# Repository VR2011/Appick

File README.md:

Appick is a 4-key macropad that allows you to launch an app from a click of a button! It's loaded to launch Brave, Spotify, Steam, and Discord. It also features an OLED display that displays what app is being launched!

**You'll need to install AutoHotkey for this to work as intended. Install it [here](https://www.autohotkey.com/).** When Autohotkey is setup, download the AHK script from the repository and edit it as instructed. 

# Screenshots
Appick 3D Model:

Schematic:

PCB:

# Bill of Materials
- 4 Cherry MX Switches
- 4 DSA Keycaps
- 4 M3x5x4 Heatset Inserts
- 4 M3x12mm SHCS Bolts
- 1 0.91" 128x32 OLED Display
- 1 XIAO RP2040 Microcontroller
- 1 Case, 2 Printed Parts

Appick was created during Hack Club's Stardance challenge.

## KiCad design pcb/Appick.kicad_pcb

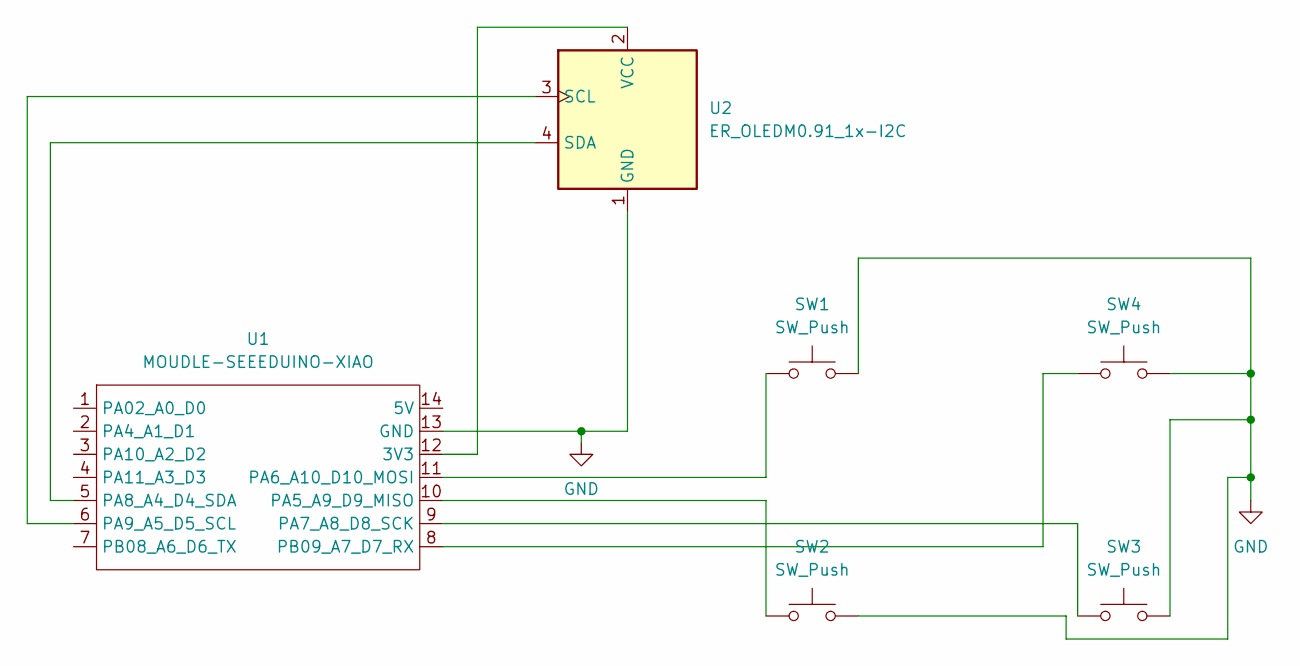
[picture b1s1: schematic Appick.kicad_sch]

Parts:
SW1, SW2, SW3, SW4: SW_Push; SW_Cherry_MX_1.00u_PCB
U1: MOUDLE-SEEEDUINO-XIAO; XIAO-Generic-Hybrid-14P-2.54-21X17.8MM
U2: ER_OLEDM0.91_1x-I2C

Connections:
GND: SW1.2, SW2.2, SW3.2, SW4.2, U1.13 (GND), U2.1 (GND)
unnamed: U1.12 (3V3), U2.2 (VCC)
unnamed: SW2.1, U1.10 (PA5_A9_D9_MISO)
unnamed: SW1.1, U1.11 (PA6_A10_D10_MOSI)
unnamed: SW3.1, U1.9 (PA7_A8_D8_SCK)
unnamed: U1.5 (PA8_A4_D4_SDA), U2.4 (SDA)
unnamed: U1.6 (PA9_A5_D5_SCL), U2.3 (SCL)
unnamed: SW4.1, U1.8 (PB09_A7_D7_RX)

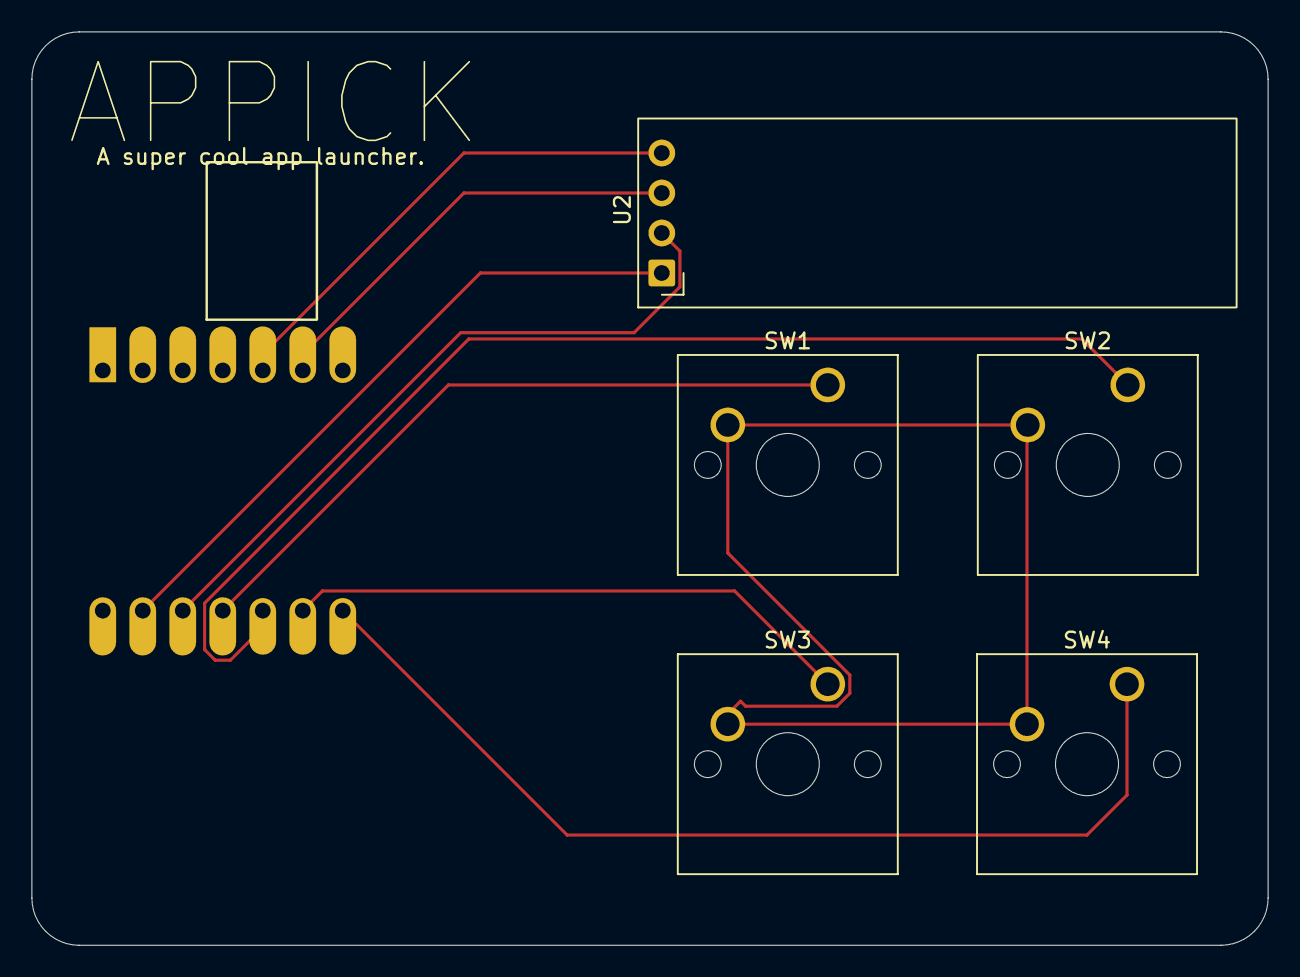
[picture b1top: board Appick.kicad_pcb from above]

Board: 2 copper layers, 78.5 x 58.0 mm, 6 parts (1 on the bottom side), 8 nets.

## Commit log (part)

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2026-06-23 Init
2026-06-23 placeholder readme, will add everything soon
2026-06-23 add pcb files
2026-06-23 added firmware
2026-06-23 added files correctly via firmware folder
2026-06-23 removed ctrl + alt requirement for ahk macro
2026-06-23 keymap update
2026-06-23 add config.h
2026-06-23 keyboard.json update
    Added OLED support to keyboard configuration.
2026-06-23 add rules.mk
2026-06-23 added firmware file i think thats the firmware file idk
2026-06-23 README added
    Added detailed description, screenshots, and bill of materials for Appick.
2026-06-23 appick was created during hack time's stardance
2026-06-28 added bom.csv
2026-06-28 fixed bom
